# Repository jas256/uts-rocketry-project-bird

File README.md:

# uts-rocketry-project-bird
https://git.io/JJHyt

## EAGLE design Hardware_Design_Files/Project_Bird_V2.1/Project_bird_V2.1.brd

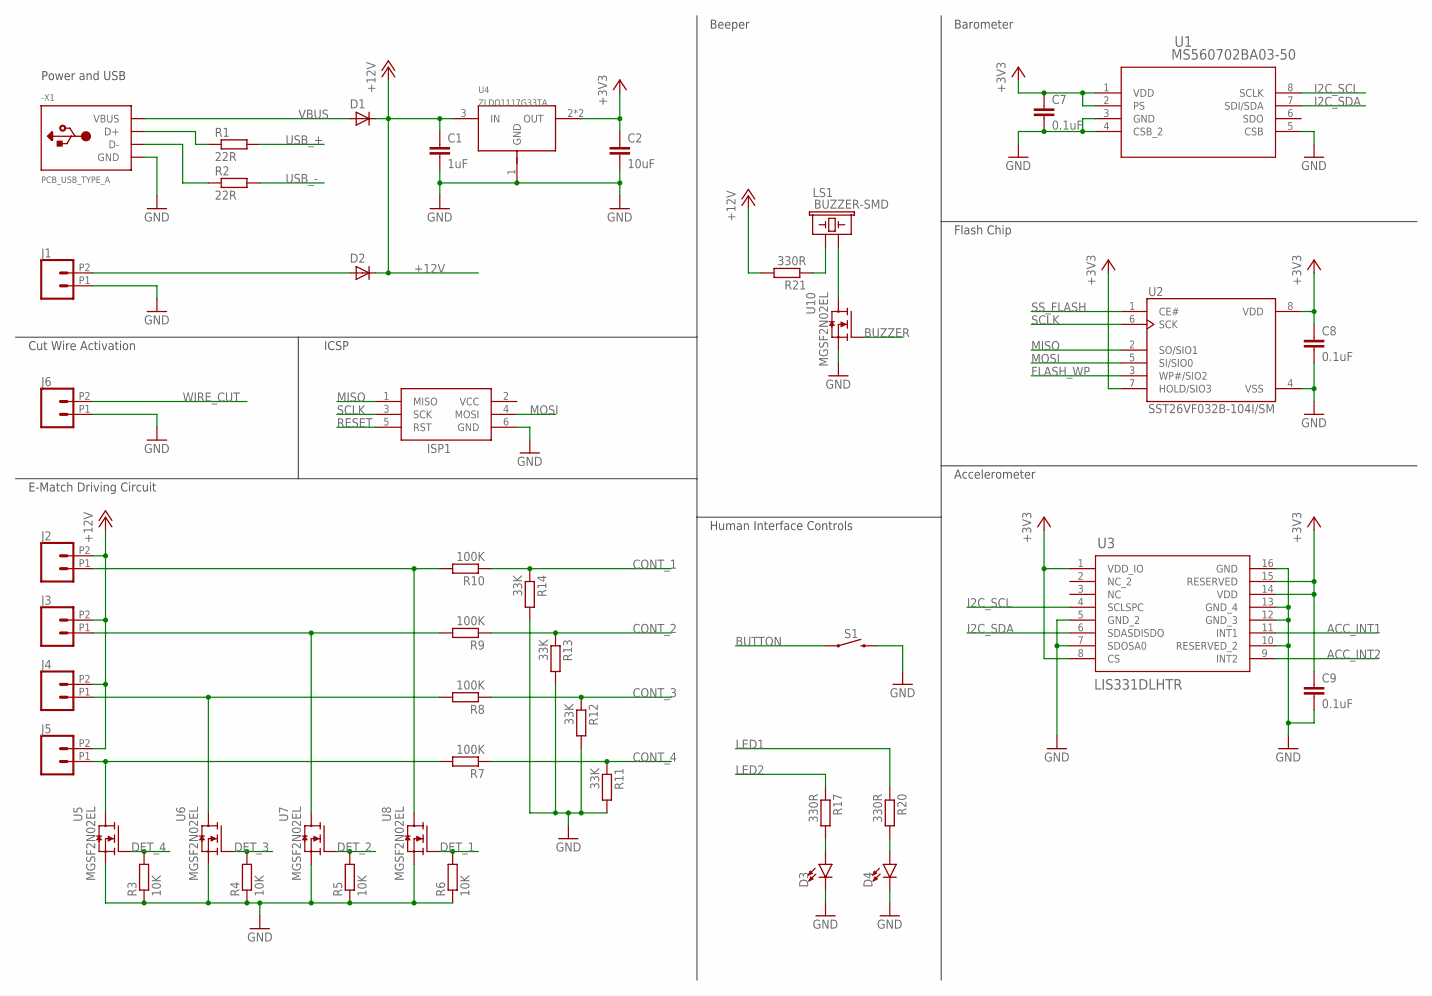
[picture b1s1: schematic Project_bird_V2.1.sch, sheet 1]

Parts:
-X1: PCB_USB_TYPE_A; USB_TYPE-A
C1: 1uF; C0805K
C2: 10uF; C0805K
C7, C8, C9: 0.1uF; C0805K
D1, D2: 1A; SOD-323F
D3: LED3MM-RED; LED_3MM
D4: LED3MM-YELLOW; LED_3MM
ISP1: AVRISP-6; AVRISP
J1, J2, J3, J4, J5, J6: CONN_022.54MM_SCREWTERM; 1X02_2.54_SCREWTERM
LS1: BUZZER-SMD; BUZZER-CCV
R1, R2: 22R; R0805
R3, R4, R5, R6: 10K; R0805
R7, R8, R9, R10: 100K; R0805
R11, R12, R13, R14: 33K; R0805
R17, R20, R21: 330R; R0805
S1: MOMENTARY-SWITCH-SPST; TACTILE_SWITCH_PTH_6.0MM
U1: MS560702BA03-50; SON8_MS5611
U2: SST26VF032B-104I/SM; SOIC127P794X203-8N
U3: LIS331DLHTR; LGA-16_3X3X1MM
U4: ZLDO1117G33TA; SOT223
U5, U6, U7, U8, U10: MGSF2N02EL; SOT-23-3

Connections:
+3V3: C2.1, C7.1, C8.1, C9.1, U1.1 (VDD), U1.2 (PS), U2.7 (HOLD/SIO3), U2.8 (VDD), U3.1 (VDD_IO), U3.8 (CS), U3.14 (VDD), U3.15 (RESERVED), U4.2 (OUT), U4.4 (OUT); also elsewhere on the board
+12V: C1.1, D1.C, D2.C, J2.P2 (2), J3.P2 (2), J4.P2 (2), J5.P2 (2), R21.2, U4.3 (IN)
ACC_INT1: U3.11 (INT1); also elsewhere on the board
ACC_INT2: U3.9 (INT2); also elsewhere on the board
BUTTON: S1.1, S1.2 (1); also elsewhere on the board
BUZZER: U10.1 (G); also elsewhere on the board
CONT_1: R10.1, R14.1; also elsewhere on the board
CONT_2: R9.1, R13.1; also elsewhere on the board
CONT_3: R8.1, R12.1; also elsewhere on the board
CONT_4: R7.1, R11.1; also elsewhere on the board
DET_1: R6.2, U8.1 (G); also elsewhere on the board
DET_2: R5.2, U7.1 (G); also elsewhere on the board
DET_3: R4.2, U6.1 (G); also elsewhere on the board
DET_4: R3.2, U5.1 (G); also elsewhere on the board
FLASH_WP: U2.3 (WP#/SIO2); also elsewhere on the board
GND: -X1.GND, C1.2, C2.2, C7.2, C8.2, C9.2, D3.K (C), D4.K (C), ISP1.6 (GND), J1.P1 (1), J6.P1 (1), R3.1, R4.1, R5.1, R6.1, R11.2, R12.2, R13.2, R14.2, S1.3 (2), S1.4 (2), U1.3 (GND), U1.4 (CSB_2), U1.5 (CSB), U2.4 (VSS), U3.5 (GND_2), U3.7 (SDOSA0), U3.10 (RESERVED_2), U3.12 (GND_3), U3.13 (GND_4), U3.16 (GND), U4.1 (GND), U5.2 (S), U6.2 (S), U7.2 (S), U8.2 (S), U10.2 (S); also elsewhere on the board
I2C_SCL: U1.8 (SCLK), U3.4 (SCLSPC); also elsewhere on the board
I2C_SDA: U1.7 (SDI/SDA), U3.6 (SDASDISDO); also elsewhere on the board
LED1: R20.1; also elsewhere on the board
LED2: R17.1; also elsewhere on the board
MISO: ISP1.1 (MISO), U2.2 (SO/SIO1); also elsewhere on the board
MOSI: ISP1.4 (MOSI), U2.5 (SI/SIO0); also elsewhere on the board
unnamed: D2.A, J1.P2 (2)
unnamed: D3.A, R17.2
unnamed: -X1.D+, R1.1
unnamed: D4.A, R20.2
unnamed: -X1.D-, R2.1
unnamed: LS1.- (2), U10.3 (D)
unnamed: LS1.+ (1), R21.1
unnamed: J5.P1 (1), R7.2, U5.3 (D)
unnamed: J4.P1 (1), R8.2, U6.3 (D)
unnamed: J3.P1 (1), R9.2, U7.3 (D)
unnamed: J2.P1 (1), R10.2, U8.3 (D)
RESET: ISP1.5 (RST); also elsewhere on the board
SCLK: ISP1.3 (SCK), U2.6 (SCK); also elsewhere on the board
SS_FLASH: U2.1 (CE#); also elsewhere on the board
USB_+: R1.2; also elsewhere on the board
USB_-: R2.2; also elsewhere on the board
VBUS: -X1.VBUS, D1.A; also elsewhere on the board
VCC: ISP1.2 (VCC)
WIRE_CUT: J6.P2 (2); also elsewhere on the board

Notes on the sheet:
Power and USB
Cut Wire Activation
ICSP
E-Match Driving Circuit
Beeper
Human Interface Controls
Barometer
Flash Chip
Accelerometer

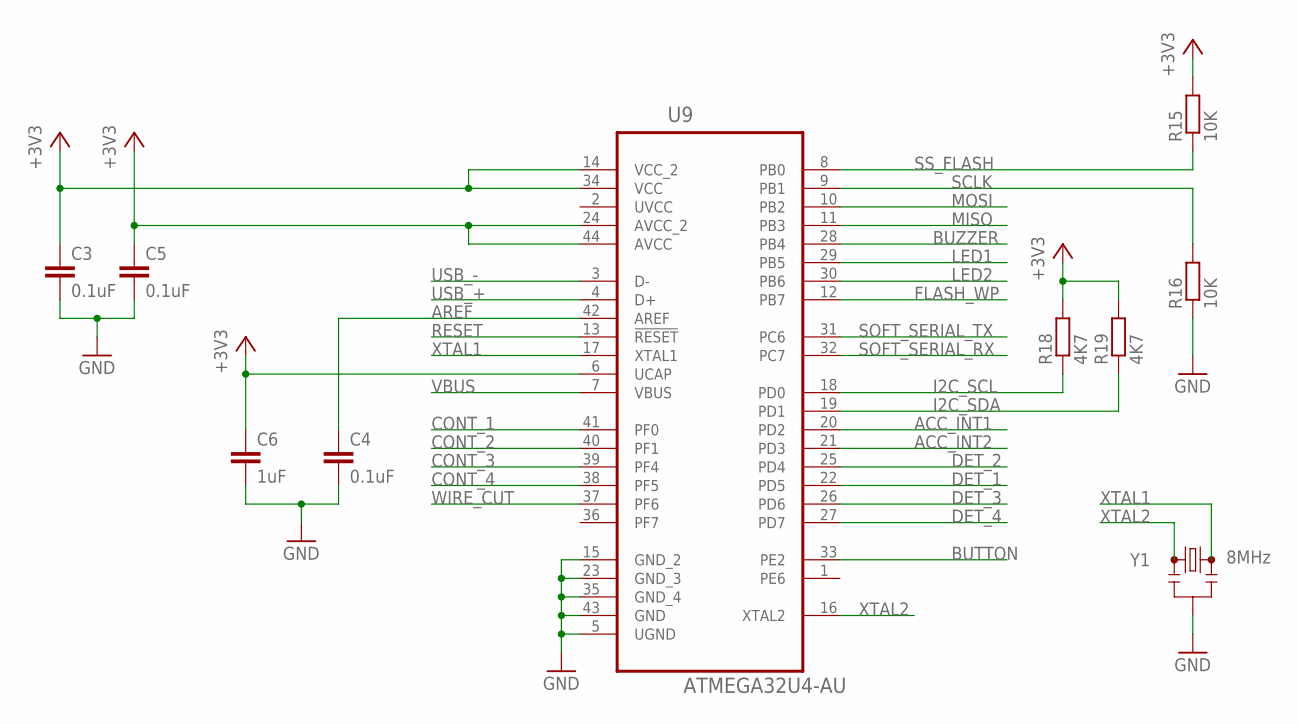
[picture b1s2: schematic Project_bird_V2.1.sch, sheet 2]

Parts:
C3, C4, C5: 0.1uF; C0805K
C6: 1uF; C0805K
R15, R16: 10K; R0805
R18, R19: 4K7; R0805
U9: ATMEGA32U4-AU; QFP80P1200X1200X120-44N
Y1: 8MHz; RESONATOR-SMD-3.2X1.3

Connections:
+3V3: C3.1, C5.1, C6.1, R15.2, R18.2, R19.2, U9.6 (UCAP), U9.14 (VCC_2), U9.24 (AVCC_2), U9.34 (VCC), U9.44 (AVCC); also elsewhere on the board
ACC_INT1: U9.20 (PD2); also elsewhere on the board
ACC_INT2: U9.21 (PD3); also elsewhere on the board
AREF: C4.1, U9.42 (AREF)
BUTTON: U9.33 (PE2); also elsewhere on the board
BUZZER: U9.28 (PB4); also elsewhere on the board
CONT_1: U9.41 (PF0); also elsewhere on the board
CONT_2: U9.40 (PF1); also elsewhere on the board
CONT_3: U9.39 (PF4); also elsewhere on the board
CONT_4: U9.38 (PF5); also elsewhere on the board
DET_1: U9.22 (PD5); also elsewhere on the board
DET_2: U9.25 (PD4); also elsewhere on the board
DET_3: U9.26 (PD6); also elsewhere on the board
DET_4: U9.27 (PD7); also elsewhere on the board
FLASH_WP: U9.12 (PB7); also elsewhere on the board
GND: C3.2, C4.2, C5.2, C6.2, R16.1, U9.5 (UGND), U9.15 (GND_2), U9.23 (GND_3), U9.35 (GND_4), U9.43 (GND), Y1.2; also elsewhere on the board
I2C_SCL: R18.1, U9.18 (PD0); also elsewhere on the board
I2C_SDA: R19.1, U9.19 (PD1); also elsewhere on the board
LED1: U9.29 (PB5); also elsewhere on the board
LED2: U9.30 (PB6); also elsewhere on the board
MISO: U9.11 (PB3); also elsewhere on the board
MOSI: U9.10 (PB2); also elsewhere on the board
RESET: U9.13 (!RESET); also elsewhere on the board
SCLK: R16.2, U9.9 (PB1); also elsewhere on the board
SOFT_SERIAL_RX: U9.32 (PC7)
SOFT_SERIAL_TX: U9.31 (PC6)
SS_FLASH: R15.1, U9.8 (PB0); also elsewhere on the board
USB_+: U9.4 (D+); also elsewhere on the board
USB_-: U9.3 (D-); also elsewhere on the board
UVCC: U9.2 (UVCC)
VBUS: U9.7 (VBUS); also elsewhere on the board
WIRE_CUT: U9.37 (PF6); also elsewhere on the board
XTAL1: U9.17 (XTAL1), Y1.3
XTAL2: U9.16 (XTAL2), Y1.1

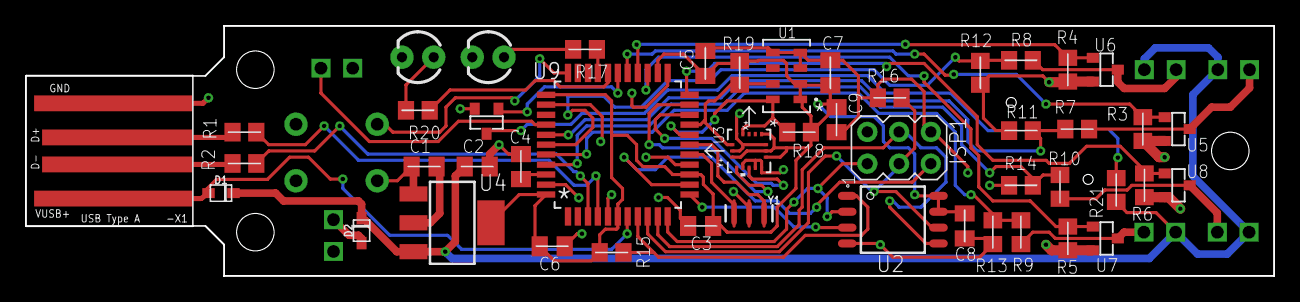
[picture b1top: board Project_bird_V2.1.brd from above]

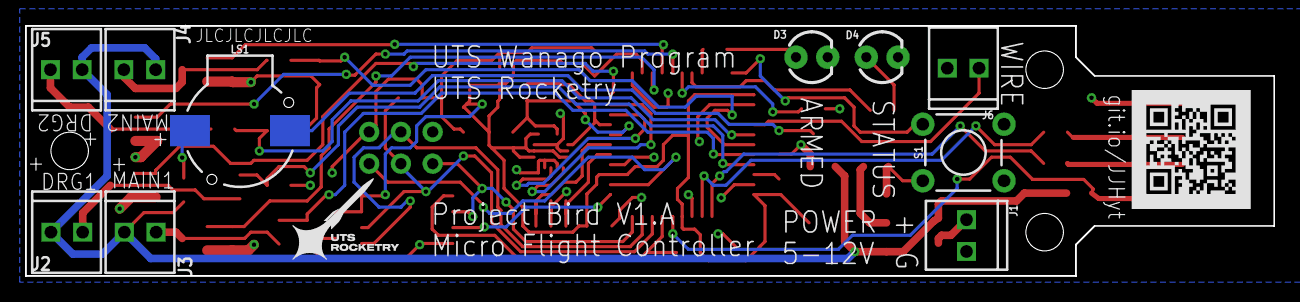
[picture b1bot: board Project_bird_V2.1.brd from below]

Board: 2 copper layers, 99.9 x 20.0 mm, 55 parts (10 on the bottom side), 43 nets.

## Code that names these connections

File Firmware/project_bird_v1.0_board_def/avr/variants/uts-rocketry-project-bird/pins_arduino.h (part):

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
// ATMEL ATMEGA32U4 / ARDUINO LEONARDO
//
// D0				PD2					RXD1/INT2
// D1				PD3					TXD1/INT3
// D2				PD1		SDA			SDA/INT1
// D3#				PD0		PWM8/SCL	OC0B/SCL/INT0
// D4		A6		PD4					ADC8
// D5#				PC6		???			OC3A/#OC4A
// D6#		A7		PD7		FastPWM		#OC4D/ADC10
// D7				PE6					INT6/AIN0
//
// D8		A8		PB4					ADC11/PCINT4
// D9#		A9		PB5		PWM16		OC1A/#OC4B/ADC12/PCINT5
// D10#		A10		PB6		PWM16		OC1B/0c4B/ADC13/PCINT6
// D11#				PB7		PWM8/16		0C0A/OC1C/#RTS/PCINT7
// D12		A11		PD6					T1/#OC4D/ADC9
// D13#				PC7		PWM10		CLK0/OC4A
//
// A0		D18		PF7					ADC7
// A1		D19		PF6					ADC6
// A2		D20 	PF5					ADC5
// A3		D21 	PF4					ADC4
// A4		D22		PF1					ADC1
// A5		D23 	PF0					ADC0
//
// New pins D14..D17 to map SPI port to digital pins
//
// MISO		D14		PB3					MISO,PCINT3
// SCK		D15		PB1					SCK,PCINT1
// MOSI		D16		PB2					MOSI,PCINT2
// SS		D17		PB0					RXLED,SS/PCINT0
//
// TXLED	D30		PD5					XCK1
// RXLED	D17	    PB0
// HWB				PE2					HWB

// these arrays map port names (e.g. port B) to the
// appropriate addresses for various functions (e.g. reading
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};

const uint8_t PROGMEM digital_pin_to_port_PGM[] = {
	PD, // D0 - PD2
	PD,	// D1 - PD3
	PD, // D2 - PD1
	PD,	// D3 - PD0
	PD,	// D4 - PD4
	PC, // D5 - PC6
	PD, // D6 - PD7
	PE, // D7 - PE6
	
	PB, // D8 - PB4
	PB,	// D9 - PB5
	PB, // D10 - PB6
	PB,	// D11 - PB7
	PD, // D12 - PD6
	PC, // D13 - PC7
	
	PB,	// D14 - MISO - PB3
	PB,	// D15 - SCK - PB1
	PB,	// D16 - MOSI - PB2
	PB,	// D17 - SS - PB0
	
	PF,	// D18 - A0 - PF7
	PF, // D19 - A1 - PF6
	PF, // D20 - A2 - PF5
	PF, // D21 - A3 - PF4
	PF, // D22 - A4 - PF1
	PF, // D23 - A5 - PF0
	
	PD, // D24 / D4 - A6 - PD4
	PD, // D25 / D6 - A7 - PD7
	PB, // D26 / D8 - A8 - PB4
	PB, // D27 / D9 - A9 - PB5
	PB, // D28 / D10 - A10 - PB6
	PD, // D29 / D12 - A11 - PD6
	PD, // D30 / TX Led - PD5
	PE, // D31 / PE2 - HWB
};

const uint8_t PROGMEM digital_pin_to_bit_mask_PGM[] = {
	_BV(2), // D0 - PD2
	_BV(3),	// D1 - PD3
	_BV(1), // D2 - PD1
	_BV(0),	// D3 - PD0
	_BV(4),	// D4 - PD4
	_BV(6), // D5 - PC6
	_BV(7), // D6 - PD7
	_BV(6), // D7 - PE6
	
	_BV(4), // D8 - PB4
	_BV(5),	// D9 - PB5
	_BV(6), // D10 - PB6
	_BV(7),	// D11 - PB7
	_BV(6), // D12 - PD6
	_BV(7), // D13 - PC7
	
	_BV(3),	// D14 - MISO - PB3
	_BV(1),	// D15 - SCK - PB1
	_BV(2),	// D16 - MOSI - PB2
	_BV(0),	// D17 - SS - PB0
	
	_BV(7),	// D18 - A0 - PF7
	_BV(6), // D19 - A1 - PF6
	_BV(5), // D20 - A2 - PF5
	_BV(4), // D21 - A3 - PF4
	_BV(1), // D22 - A4 - PF1
	_BV(0), // D23 - A5 - PF0
	
	_BV(4), // D24 / D4 - A6 - PD4
	_BV(7), // D25 / D6 - A7 - PD7
	_BV(4), // D26 / D8 - A8 - PB4
	_BV(5), // D27 / D9 - A9 - PB5
	_BV(6), // D28 / D10 - A10 - PB6
	_BV(6), // D29 / D12 - A11 - PD6
	_BV(5), // D30 / TX Led - PD5
	_BV(2), // D31 / PE2 - HWB
};

const uint8_t PROGMEM digital_pin_to_timer_PGM[] = {
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
const uint8_t PROGMEM analog_pin_to_channel_PGM[] = {
	7,	// A0				PF7					ADC7
	6,	// A1				PF6					ADC6	
	5,	// A2				PF5					ADC5	
	4,	// A3				PF4					ADC4
	1,	// A4				PF1					ADC1	
	0,	// A5				PF0					ADC0	
	8,	// A6		D4		PD4					ADC8
	10,	// A7		D6		PD7					ADC10
	11,	// A8		D8		PB4					ADC11
	12,	// A9		D9		PB5					ADC12
	13,	// A10		D10		PB6					ADC13
	9	// A11		D12		PD6					ADC9
};

#endif /* ARDUINO_MAIN */
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
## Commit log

2020-08-15 Added Hardware Design Files
2020-08-16 Added Custom Core for Rocket Board
2020-08-16 Added Board Definition Header
2020-08-16 Initial Operational Code
2020-08-29 Created Flight Recorder Library to handle flight stats and flash recording.
2020-08-31 Cleanup
2020-08-31 Remove Core DL Files
2020-08-31 Added Core Folder to git ignore
2020-08-31 Changed platformio.ini to use custon packages
2020-09-05 MVP Completed
2020-09-05 Part of previous commit
2020-09-05 Basic Record and Deploy Completed (Deploy Not Tested)
2020-09-05 Fixed Bugs and Fine Tuned Deployment
2020-09-06 Reduced Program Size and Fixed Hardware 3D CAD
2022-10-29 Finally Fixed

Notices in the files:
Firmware/project_bird_v1.0_board_def/avr/variants/uts-rocketry-project-bird/pins_arduino.h:
Copyright (c) 2007 David A. Mellis
Public License along with this library; if not, write to the
Free Software Foundation, Inc., 59 Temple Place, Suite 330,
Boston, MA  02111-1307  USA
parts and their libraries:
COPYRIGHT: Copyright (C) 2016 Accelerated Designs. All rights reserved
